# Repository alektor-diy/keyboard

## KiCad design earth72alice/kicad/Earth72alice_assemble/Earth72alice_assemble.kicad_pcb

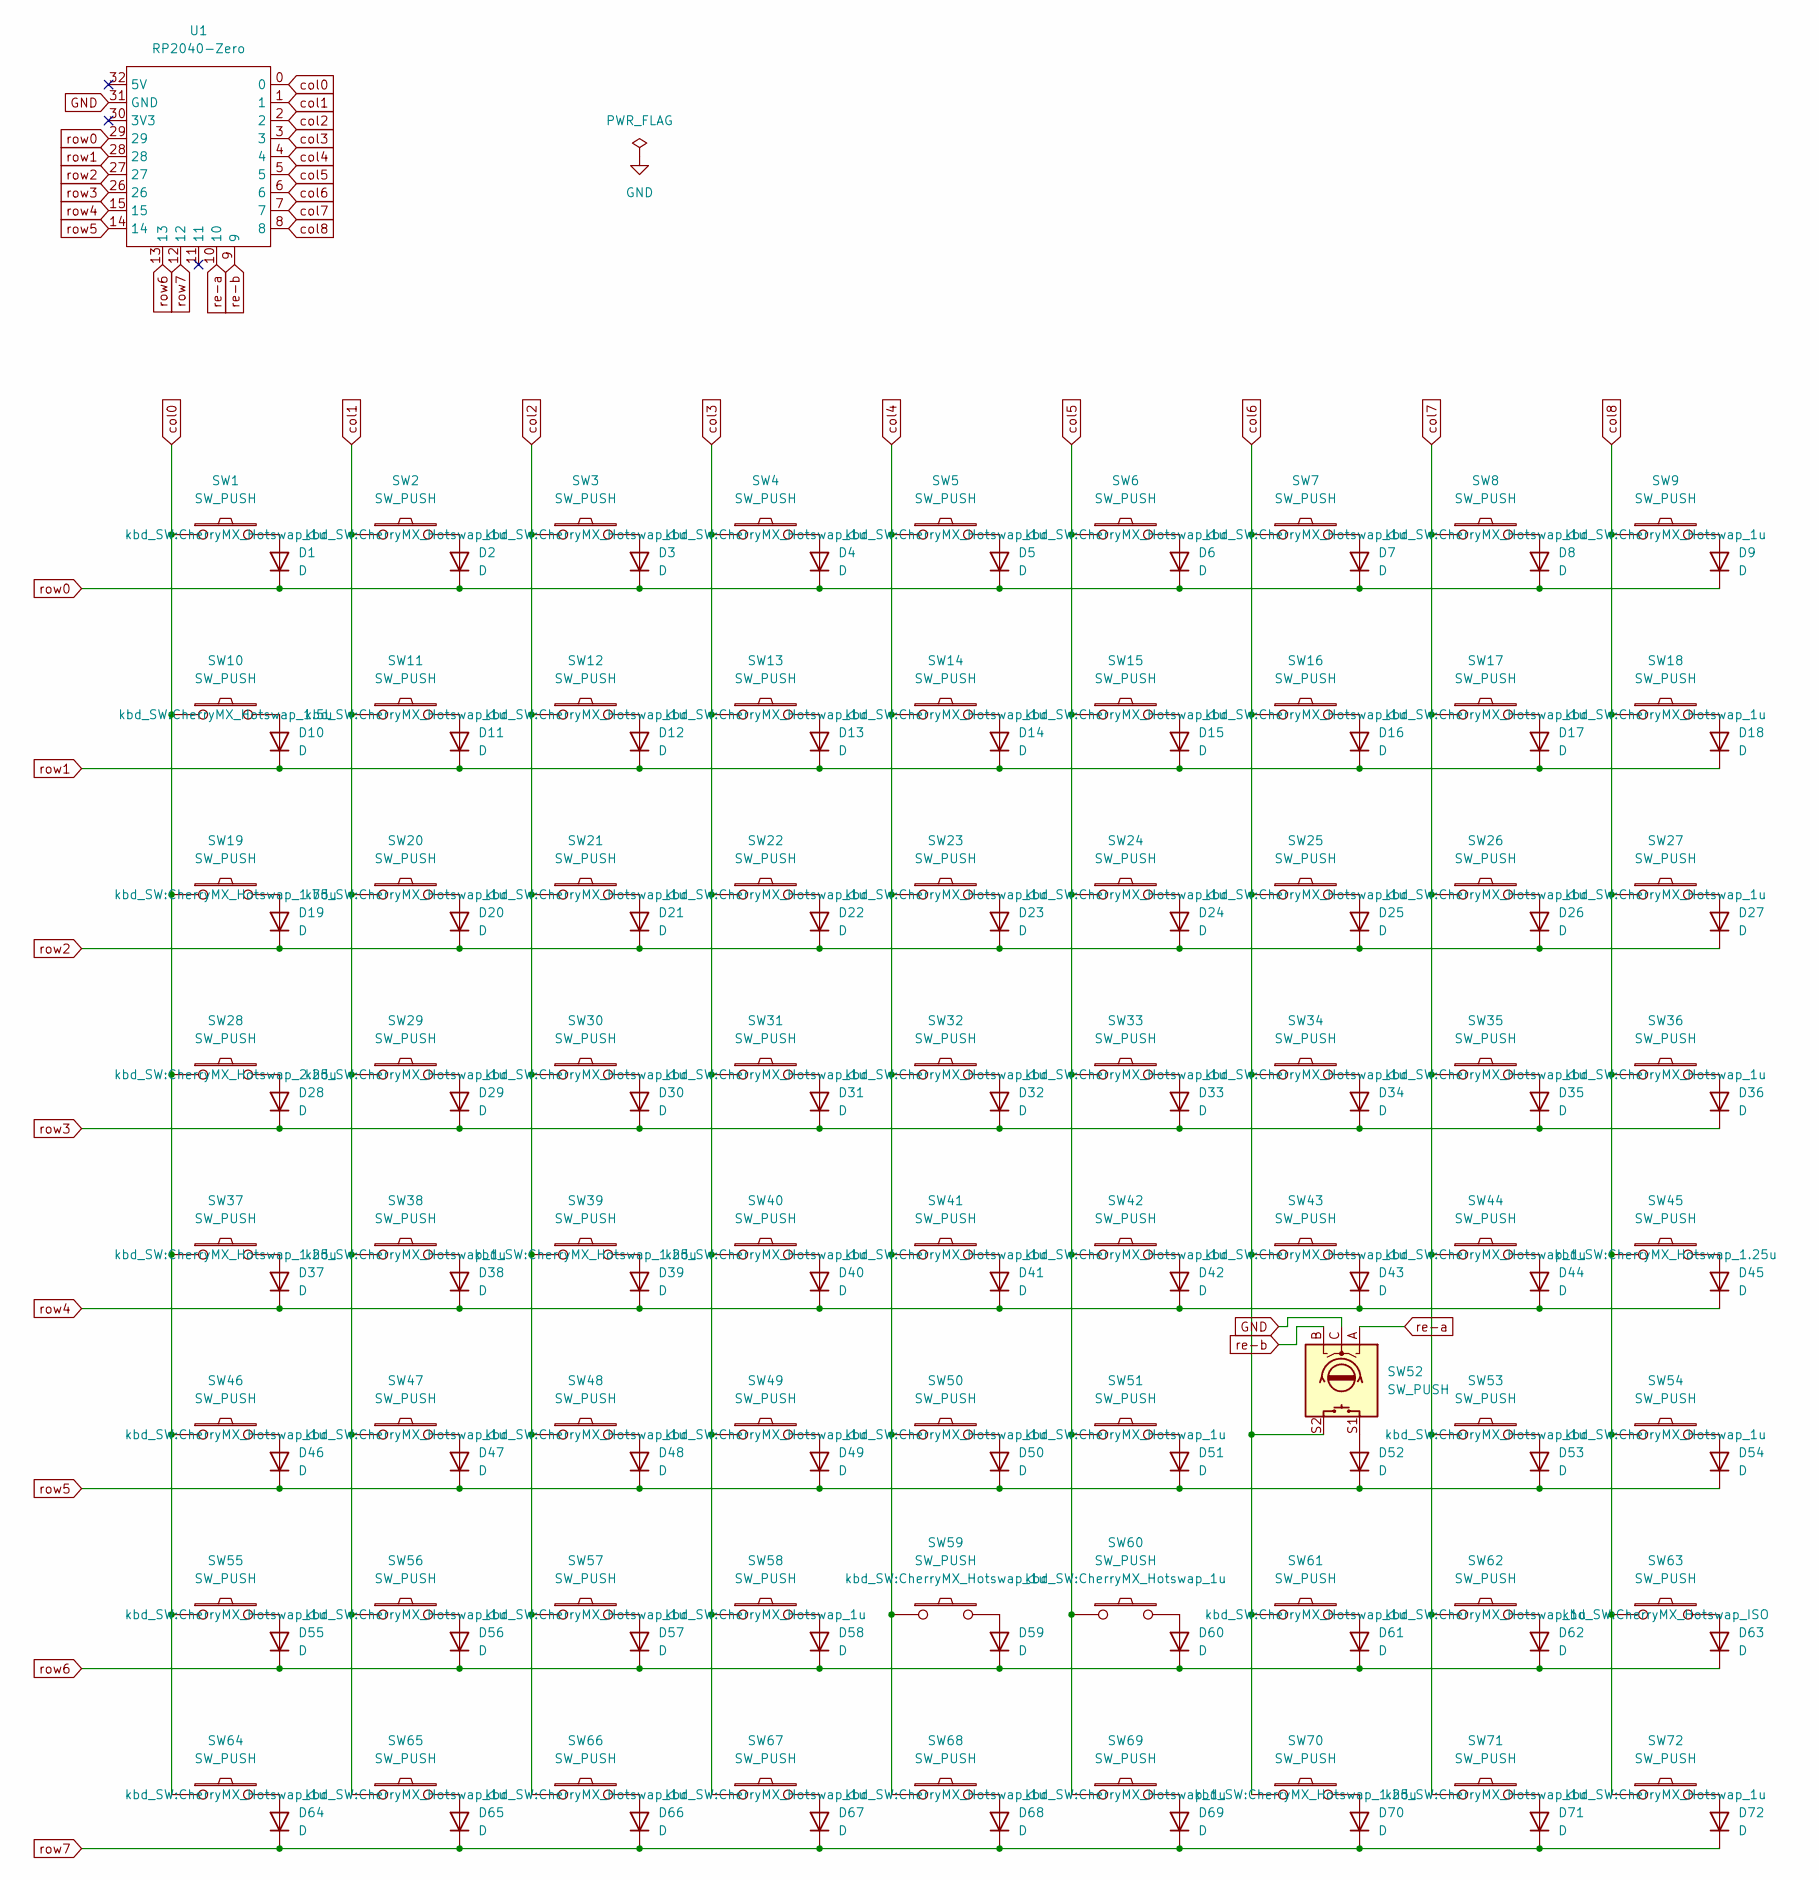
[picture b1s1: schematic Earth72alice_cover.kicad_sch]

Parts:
D1, D2, D3, D4, D5, D6, D7, D8, D9, D10, D11, D12, D13, D14, D15, D16, D17, D18, D19, D20, D21, D22, D23, D24, D25, D26, D27, D28, D29, D30, D31, D32, D33, D34, D35, D36, D37, D38, D39, D40, D41, D42, D43, D44, D45, D46, D47, D48, D49, D50, D51, D52, D53, D54, D55, D56, D57, D58, D59, D60, D61, D62, D63, D64, D65, D66, D67, D68, D69, D70, D71, D72: D; Diode_TH_SMD
SW1, SW2, SW3, SW4, SW5, SW6, SW7, SW8, SW9, SW11, SW12, SW13, SW14, SW15, SW16, SW17, SW18, SW20, SW21, SW22, SW23, SW24, SW25, SW26, SW27, SW29, SW30, SW31, SW32, SW33, SW34, SW35, SW36, SW38, SW40, SW41, SW42, SW43, SW44, SW46, SW47, SW48, SW49, SW50, SW51, SW53, SW54, SW55, SW56, SW57, SW58, SW59, SW60, SW61, SW62, SW64, SW65, SW66, SW67, SW68, SW69, SW71, SW72: SW_PUSH; CherryMX_Hotswap_1u
SW10: SW_PUSH; CherryMX_Hotswap_1.5u
SW19: SW_PUSH; CherryMX_Hotswap_1.75u
SW28: SW_PUSH; CherryMX_Hotswap_2.25u
SW37, SW39, SW45, SW70: SW_PUSH; CherryMX_Hotswap_1.25u
SW52: SW_PUSH; RotaryEncoder_EC12E
SW63: SW_PUSH; CherryMX_Hotswap_ISO
U1: RP2040-Zero; RP2040-Zero-THT

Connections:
GND: SW52.C, U1.31 (GND)
unnamed: D1.2 (A), SW1.2
unnamed: D2.2 (A), SW2.2
unnamed: D3.2 (A), SW3.2
unnamed: D4.2 (A), SW4.2
unnamed: D5.2 (A), SW5.2
unnamed: D6.2 (A), SW6.2
unnamed: D7.2 (A), SW7.2
unnamed: D8.2 (A), SW8.2
unnamed: D9.2 (A), SW9.2
unnamed: D10.2 (A), SW10.2
unnamed: D11.2 (A), SW11.2
unnamed: D12.2 (A), SW12.2
unnamed: D13.2 (A), SW13.2
unnamed: D14.2 (A), SW14.2
unnamed: D15.2 (A), SW15.2
unnamed: D16.2 (A), SW16.2
unnamed: D17.2 (A), SW17.2
unnamed: D18.2 (A), SW18.2
unnamed: D19.2 (A), SW19.2
unnamed: D20.2 (A), SW20.2
unnamed: D21.2 (A), SW21.2
unnamed: D22.2 (A), SW22.2
unnamed: D23.2 (A), SW23.2
unnamed: D24.2 (A), SW24.2
unnamed: D25.2 (A), SW25.2
unnamed: D26.2 (A), SW26.2
unnamed: D27.2 (A), SW27.2
unnamed: D28.2 (A), SW28.2
unnamed: D29.2 (A), SW29.2
unnamed: D30.2 (A), SW30.2
unnamed: D31.2 (A), SW31.2
unnamed: D32.2 (A), SW32.2
unnamed: D33.2 (A), SW33.2
unnamed: D34.2 (A), SW34.2
unnamed: D35.2 (A), SW35.2
unnamed: D36.2 (A), SW36.2
unnamed: D37.2 (A), SW37.2
unnamed: D38.2 (A), SW38.2
unnamed: D39.2 (A), SW39.2
unnamed: D40.2 (A), SW40.2
unnamed: D41.2 (A), SW41.2
unnamed: D42.2 (A), SW42.2
unnamed: D43.2 (A), SW43.2
unnamed: D44.2 (A), SW44.2
unnamed: D45.2 (A), SW45.2
unnamed: D46.2 (A), SW46.2
unnamed: D47.2 (A), SW47.2
unnamed: D48.2 (A), SW48.2
unnamed: D49.2 (A), SW49.2
unnamed: D50.2 (A), SW50.2
unnamed: D51.2 (A), SW51.2
unnamed: D52.2 (A), SW52.S1
unnamed: D53.2 (A), SW53.2
unnamed: D54.2 (A), SW54.2
unnamed: D55.2 (A), SW55.2
unnamed: D56.2 (A), SW56.2
unnamed: D57.2 (A), SW57.2
unnamed: D58.2 (A), SW58.2
unnamed: D59.2 (A), SW59.2
unnamed: D60.2 (A), SW60.2
unnamed: D61.2 (A), SW61.2
unnamed: D62.2 (A), SW62.2
unnamed: D63.2 (A), SW63.2
unnamed: D64.2 (A), SW64.2
unnamed: D65.2 (A), SW65.2
unnamed: D66.2 (A), SW66.2
unnamed: D67.2 (A), SW67.2
unnamed: D68.2 (A), SW68.2
unnamed: D69.2 (A), SW69.2
unnamed: D70.2 (A), SW70.2
unnamed: D71.2 (A), SW71.2
unnamed: D72.2 (A), SW72.2
col0: SW1.1, SW10.1, SW19.1, SW28.1, SW37.1, SW46.1, SW55.1, SW64.1, U1.0
col1: SW2.1, SW11.1, SW20.1, SW29.1, SW38.1, SW47.1, SW56.1, SW65.1, U1.1
col2: SW3.1, SW12.1, SW21.1, SW30.1, SW39.1, SW48.1, SW57.1, SW66.1, U1.2
col3: SW4.1, SW13.1, SW22.1, SW31.1, SW40.1, SW49.1, SW58.1, SW67.1, U1.3
col4: SW5.1, SW14.1, SW23.1, SW32.1, SW41.1, SW50.1, SW59.1, SW68.1, U1.4
col5: SW6.1, SW15.1, SW24.1, SW33.1, SW42.1, SW51.1, SW60.1, SW69.1, U1.5
col6: SW7.1, SW16.1, SW25.1, SW34.1, SW43.1, SW52.S2, SW61.1, SW70.1, U1.6
col7: SW8.1, SW17.1, SW26.1, SW35.1, SW44.1, SW53.1, SW62.1, SW71.1, U1.7
col8: SW9.1, SW18.1, SW27.1, SW36.1, SW45.1, SW54.1, SW63.1, SW72.1, U1.8
re-a: SW52.A, U1.10
re-b: SW52.B, U1.9
row0: D1.1 (K), D2.1 (K), D3.1 (K), D4.1 (K), D5.1 (K), D6.1 (K), D7.1 (K), D8.1 (K), D9.1 (K), U1.29
row1: D10.1 (K), D11.1 (K), D12.1 (K), D13.1 (K), D14.1 (K), D15.1 (K), D16.1 (K), D17.1 (K), D18.1 (K), U1.28
row2: D19.1 (K), D20.1 (K), D21.1 (K), D22.1 (K), D23.1 (K), D24.1 (K), D25.1 (K), D26.1 (K), D27.1 (K), U1.27
row3: D28.1 (K), D29.1 (K), D30.1 (K), D31.1 (K), D32.1 (K), D33.1 (K), D34.1 (K), D35.1 (K), D36.1 (K), U1.26
row4: D37.1 (K), D38.1 (K), D39.1 (K), D40.1 (K), D41.1 (K), D42.1 (K), D43.1 (K), D44.1 (K), D45.1 (K), U1.15
row5: D46.1 (K), D47.1 (K), D48.1 (K), D49.1 (K), D50.1 (K), D51.1 (K), D52.1 (K), D53.1 (K), D54.1 (K), U1.14
row6: D55.1 (K), D56.1 (K), D57.1 (K), D58.1 (K), D59.1 (K), D60.1 (K), D61.1 (K), D62.1 (K), D63.1 (K), U1.13
row7: D64.1 (K), D65.1 (K), D66.1 (K), D67.1 (K), D68.1 (K), D69.1 (K), D70.1 (K), D71.1 (K), D72.1 (K), U1.12

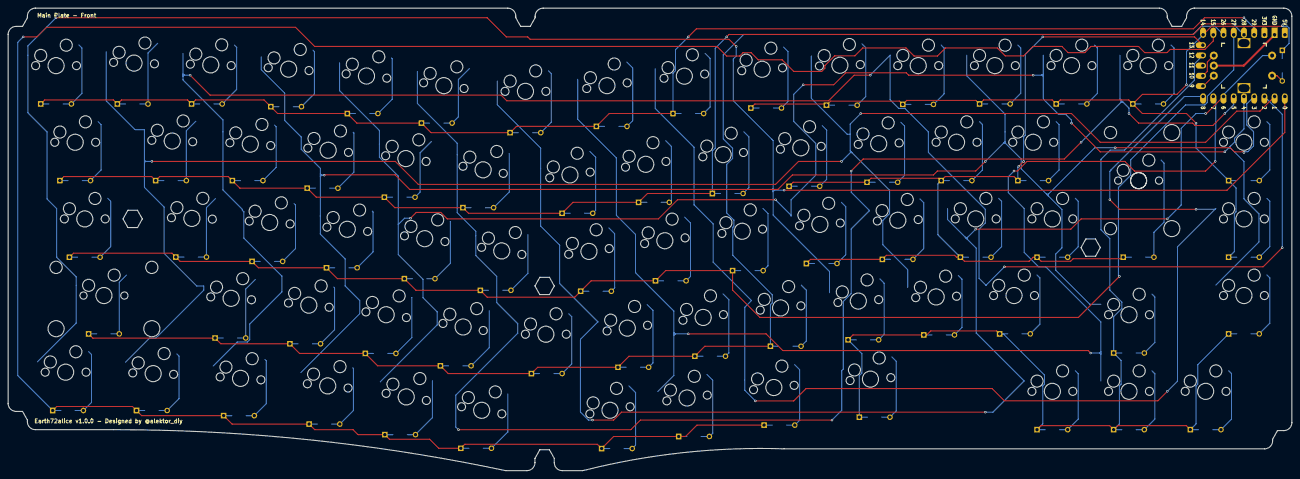
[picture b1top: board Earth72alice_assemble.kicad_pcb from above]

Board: 2 copper layers, 319.1 x 115.0 mm, 148 parts (0 on the bottom side), 92 nets.

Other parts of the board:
Ref**: Val**; m2_Spacer_Hole_hex
Ref**#2, Ref**#3: Val**; m2_Spacer_Hole_hex
